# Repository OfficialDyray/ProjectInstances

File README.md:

# Project Instances
A fork of [`HierarchicalPcb`](https://github.com/gauravmm/HierarchicalPcb) which was originally inspired by the [`ReplicateLayout`](https://github.com/MitjaNemec/ReplicateLayout) plugin.

## How To Use

https://github.com/user-attachments/assets/78d0a88c-ed20-4e0c-ae54-b3dcbba4581b

### Create a sub-project:
   1. Creating another (sub-)project inside your main project's folder. 

Here is what the recommended folder structure looks like from the root project:

   3. Create your schematic and pcb in the sub-project like normal
   4. Include the sub-project schematic in your Main Project
   5. Prepare the board like you are about to lay it out.
   6. Run the plugin on the main project's PCB to import the sub-project's PCB

### Update an existing sub-project:
   1. Make your changes to the sub-project's schematic and pcb
   2. Go to your main project and (re)annotate the sub-project's sheet.
   3. Update the pcb from your new schematics
   4. Run the plugin to apply the changes

[A Basic Example](examples/Basic)

## Tips
   1. It is intended to leave footprints out of a sub-board and they won't be laid out in the root project.

## Advanced Usage:
### [Nested Projects](examples/Nesting)
### [Variants of same project](examples/Variants)
### [And more](examples)

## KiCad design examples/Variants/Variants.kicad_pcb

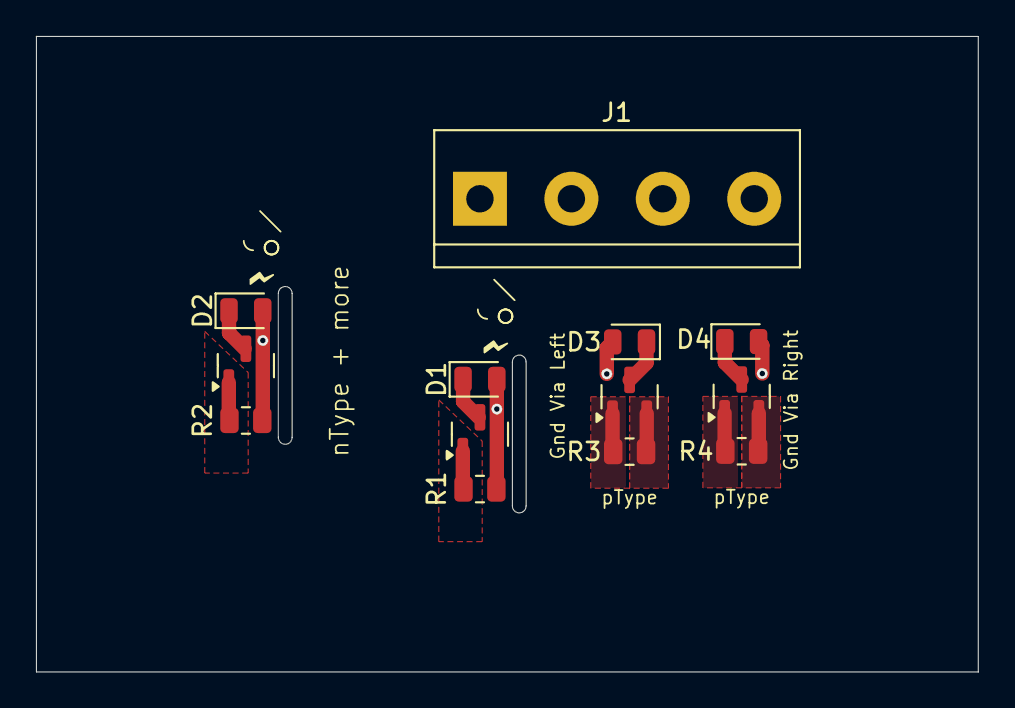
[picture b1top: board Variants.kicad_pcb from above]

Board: 2 copper layers, 52.3 x 35.3 mm, 13 parts (0 on the bottom side), 8 nets.

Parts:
D1, D2, D3, D4: D_Schottky_Small; D_0805_2012Metric
J1: Screw_Terminal_01x04; TerminalBlock_bornier-4_P5.08mm
Q1, Q2: MMBT2222A; SOT-23
Q3, Q4: BC807; SOT-23
R1, R2, R3, R4: 10k; R_0805_2012Metric

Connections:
/Input: Q1.1 (B), R1.1
/nType/Output: D1.1 (K), J1.2, Q1.3 (C), Q3.1 (B), Q4.1 (B), R3.2, R4.2
/nTypeA/Input: Q2.1 (B), R2.1
/nTypeA/Output: D2.1 (K), Q2.3 (C)
/pTypeA/Output: D4.1 (K), J1.3, Q4.3 (C)
/pTypeB/Output: D3.1 (K), J1.1, Q3.3 (C)
GND: D1.2 (A), D2.2 (A), D3.2 (A), D4.2 (A), J1.4, Q1.2 (E), Q2.2 (E), R1.2, R2.2
VDC: Q3.2 (E), Q4.2 (E), R3.1, R4.1

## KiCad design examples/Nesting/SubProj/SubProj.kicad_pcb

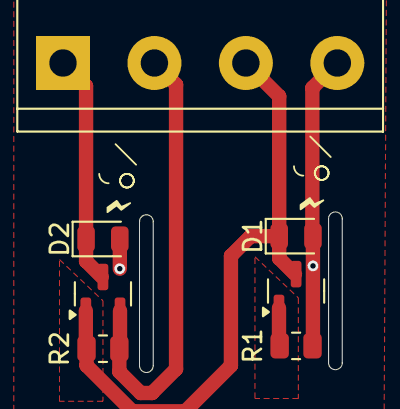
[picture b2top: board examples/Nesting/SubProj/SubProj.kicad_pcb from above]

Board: 2 copper layers, 7 parts (0 on the bottom side), 5 nets.

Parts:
D1, D2: D_Schottky_Small; D_0805_2012Metric
J1: Screw_Terminal_01x04; TerminalBlock_bornier-4_P5.08mm
Q1: MMBT2222A; SOT-23
Q2: BC807; SOT-23
R1, R2: 10k; R_0805_2012Metric

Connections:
/Input: Q1.1 (B), R1.1
/nType/Output: D1.1 (K), J1.3, Q1.3 (C), Q2.1 (B), R2.2
/pType/Output: D2.1 (K), J1.1, Q2.3 (C)
GND: D1.2 (A), D2.2 (A), J1.4, Q1.2 (E), R1.2
VDC: J1.2, Q2.2 (E), R2.1

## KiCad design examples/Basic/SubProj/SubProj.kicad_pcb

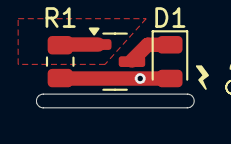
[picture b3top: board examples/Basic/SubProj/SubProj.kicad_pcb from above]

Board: 2 copper layers, 3 parts (0 on the bottom side), 3 nets.

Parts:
D1: D_Schottky_Small; D_0805_2012Metric
Q1: MMBT2222A; SOT-23
R1: 10k; R_0805_2012Metric

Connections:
/Input: Q1.1 (B), R1.1
/Output: D1.1 (K), Q1.3 (C)
GND: D1.2 (A), Q1.2 (E), R1.2

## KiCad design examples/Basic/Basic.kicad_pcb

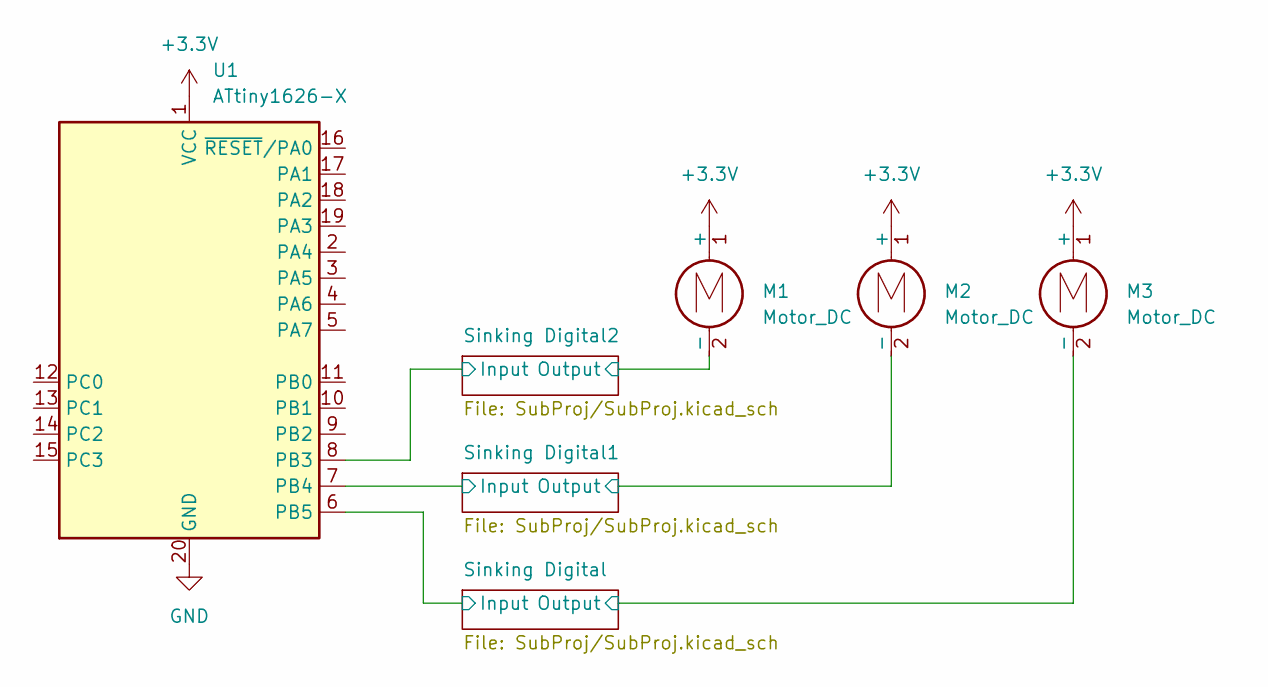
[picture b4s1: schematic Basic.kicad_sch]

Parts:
M1, M2, M3: Motor_DC; PinSocket_1x02_P2.54mm_Vertical
U1: ATtiny1626-X; SSOP-20_5.3x7.2mm_P0.65mm

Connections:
+3.3V: M1.1 (+), M2.1 (+), M3.1 (+), U1.1 (VCC)
/Sinking Digital1/Input: U1.7 (PB4); also elsewhere on the board
/Sinking Digital1/Output: M2.2 (-); also elsewhere on the board
/Sinking Digital2/Input: U1.8 (PB3); also elsewhere on the board
/Sinking Digital2/Output: M1.2 (-); also elsewhere on the board
/Sinking Digital/Input: U1.6 (PB5); also elsewhere on the board
/Sinking Digital/Output: M3.2 (-); also elsewhere on the board
GND: U1.20 (GND); also elsewhere on the board

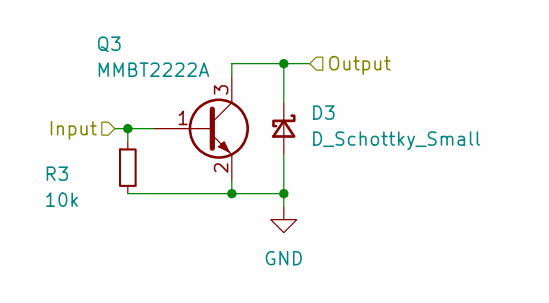
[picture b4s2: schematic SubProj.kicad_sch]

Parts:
D3: D_Schottky_Small; D_0805_2012Metric
Q3: MMBT2222A; SOT-23
R3: 10k; R_0805_2012Metric

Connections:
/Sinking Digital2/Input: Q3.1 (B), R3.1; also elsewhere on the board
/Sinking Digital2/Output: D3.1 (K), Q3.3 (C); also elsewhere on the board
GND: D3.2 (A), Q3.2 (E), R3.2; also elsewhere on the board

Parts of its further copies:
D1, D2: D_Schottky_Small; D_0805_2012Metric
Q1, Q2: MMBT2222A; SOT-23
R1, R2: 10k; R_0805_2012Metric

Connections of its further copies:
/Sinking Digital1/Input: Q2.1 (B), R2.1; also elsewhere on the board
/Sinking Digital1/Output: D2.1 (K), Q2.3 (C); also elsewhere on the board
/Sinking Digital/Input: Q1.1 (B), R1.1; also elsewhere on the board
/Sinking Digital/Output: D1.1 (K), Q1.3 (C); also elsewhere on the board
GND: D1.2 (A), D2.2 (A), Q1.2 (E), Q2.2 (E), R1.2, R2.2; also elsewhere on the board

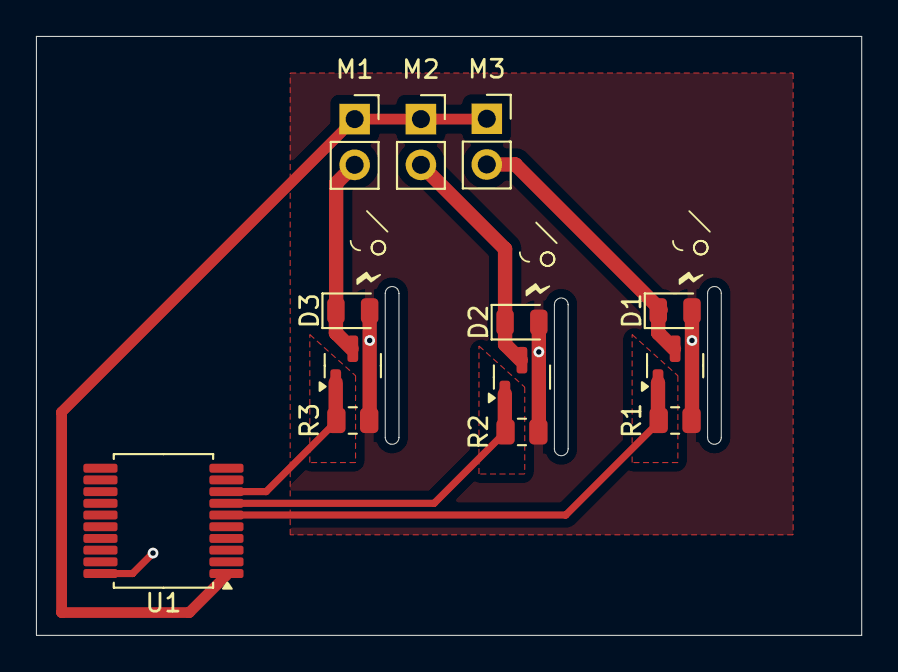
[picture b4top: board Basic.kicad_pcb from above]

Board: 2 copper layers, 45.8 x 33.3 mm, 13 parts (0 on the bottom side), 8 nets.

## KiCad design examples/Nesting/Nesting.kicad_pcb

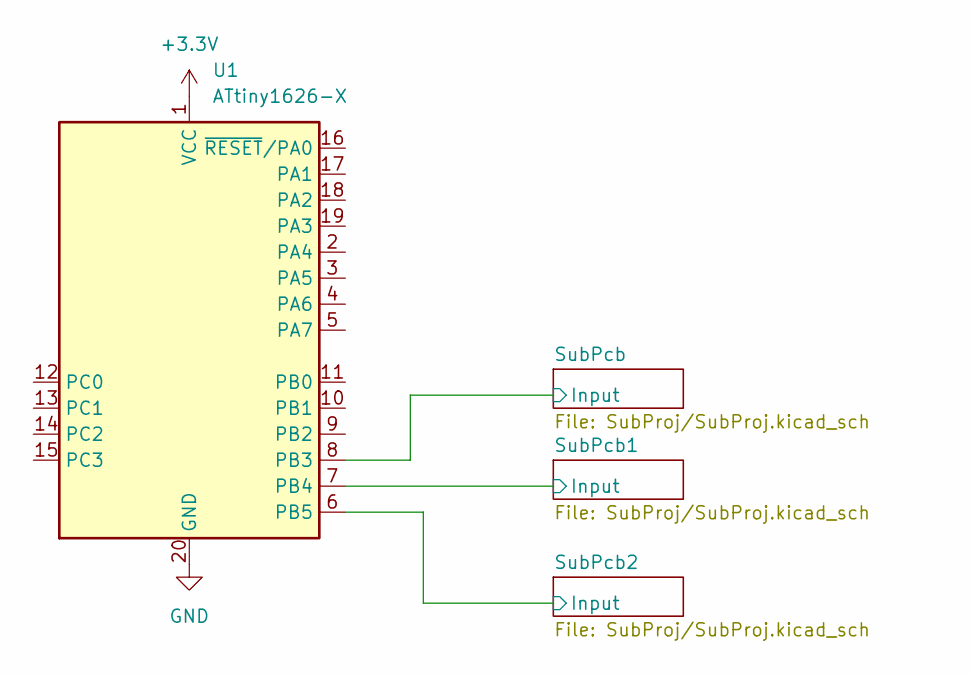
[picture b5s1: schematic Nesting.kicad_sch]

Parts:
U1: ATtiny1626-X; SSOP-20_5.3x7.2mm_P0.65mm

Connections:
+3.3V: U1.1 (VCC)
/SubPcb1/Input: U1.7 (PB4); also elsewhere on the board
/SubPcb2/Input: U1.6 (PB5); also elsewhere on the board
/SubPcb/Input: U1.8 (PB3); also elsewhere on the board
GND: U1.20 (GND); also elsewhere on the board

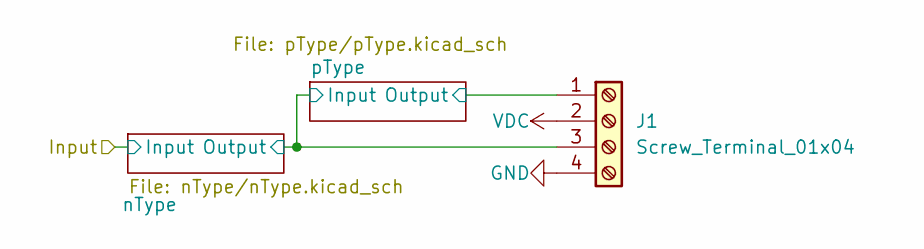
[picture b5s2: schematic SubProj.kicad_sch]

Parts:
J1: Screw_Terminal_01x04; TerminalBlock_bornier-4_P5.08mm

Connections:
/SubPcb/nType/Output: J1.3; also elsewhere on the board
/SubPcb/pType/Output: J1.1; also elsewhere on the board
GND: J1.4; also elsewhere on the board
VDC: J1.2; also elsewhere on the board

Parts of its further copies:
J2, J3: Screw_Terminal_01x04; TerminalBlock_bornier-4_P5.08mm

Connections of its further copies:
/SubPcb1/nType/Output: J2.3; also elsewhere on the board
/SubPcb1/pType/Output: J2.1; also elsewhere on the board
/SubPcb2/nType/Output: J3.3; also elsewhere on the board
/SubPcb2/pType/Output: J3.1; also elsewhere on the board
GND: J2.4, J3.4; also elsewhere on the board
VDC: J2.2, J3.2; also elsewhere on the board

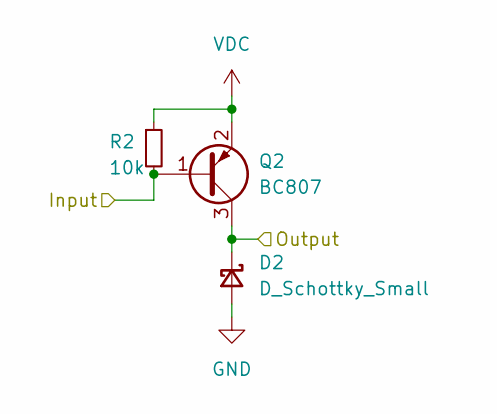
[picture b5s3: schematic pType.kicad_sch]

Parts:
D2: D_Schottky_Small; D_0805_2012Metric
Q2: BC807; SOT-23
R2: 10k; R_0805_2012Metric

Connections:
/SubPcb/nType/Output: Q2.1 (B), R2.2; also elsewhere on the board
/SubPcb/pType/Output: D2.1 (K), Q2.3 (C); also elsewhere on the board
GND: D2.2 (A); also elsewhere on the board
VDC: Q2.2 (E), R2.1; also elsewhere on the board

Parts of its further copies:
D4, D6: D_Schottky_Small; D_0805_2012Metric
Q4, Q6: BC807; SOT-23
R4, R6: 10k; R_0805_2012Metric

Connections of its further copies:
/SubPcb1/nType/Output: Q4.1 (B), R4.2; also elsewhere on the board
/SubPcb1/pType/Output: D4.1 (K), Q4.3 (C); also elsewhere on the board
/SubPcb2/nType/Output: Q6.1 (B), R6.2; also elsewhere on the board
/SubPcb2/pType/Output: D6.1 (K), Q6.3 (C); also elsewhere on the board
GND: D4.2 (A), D6.2 (A); also elsewhere on the board
VDC: Q4.2 (E), Q6.2 (E), R4.1, R6.1; also elsewhere on the board

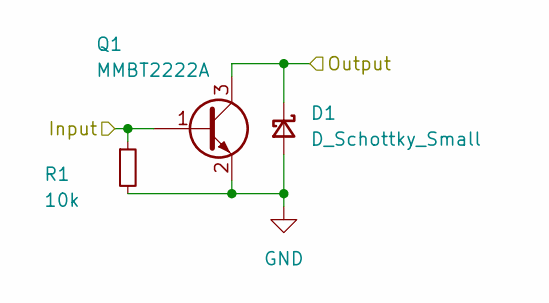
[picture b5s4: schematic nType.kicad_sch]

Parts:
D1: D_Schottky_Small; D_0805_2012Metric
Q1: MMBT2222A; SOT-23
R1: 10k; R_0805_2012Metric

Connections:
/SubPcb/Input: Q1.1 (B), R1.1; also elsewhere on the board
/SubPcb/nType/Output: D1.1 (K), Q1.3 (C); also elsewhere on the board
GND: D1.2 (A), Q1.2 (E), R1.2; also elsewhere on the board

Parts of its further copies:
D3, D5: D_Schottky_Small; D_0805_2012Metric
Q3, Q5: MMBT2222A; SOT-23
R3, R5: 10k; R_0805_2012Metric

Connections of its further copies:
/SubPcb1/Input: Q3.1 (B), R3.1; also elsewhere on the board
/SubPcb1/nType/Output: D3.1 (K), Q3.3 (C); also elsewhere on the board
/SubPcb2/Input: Q5.1 (B), R5.1; also elsewhere on the board
/SubPcb2/nType/Output: D5.1 (K), Q5.3 (C); also elsewhere on the board
GND: D3.2 (A), D5.2 (A), Q3.2 (E), Q5.2 (E), R3.2, R5.2; also elsewhere on the board

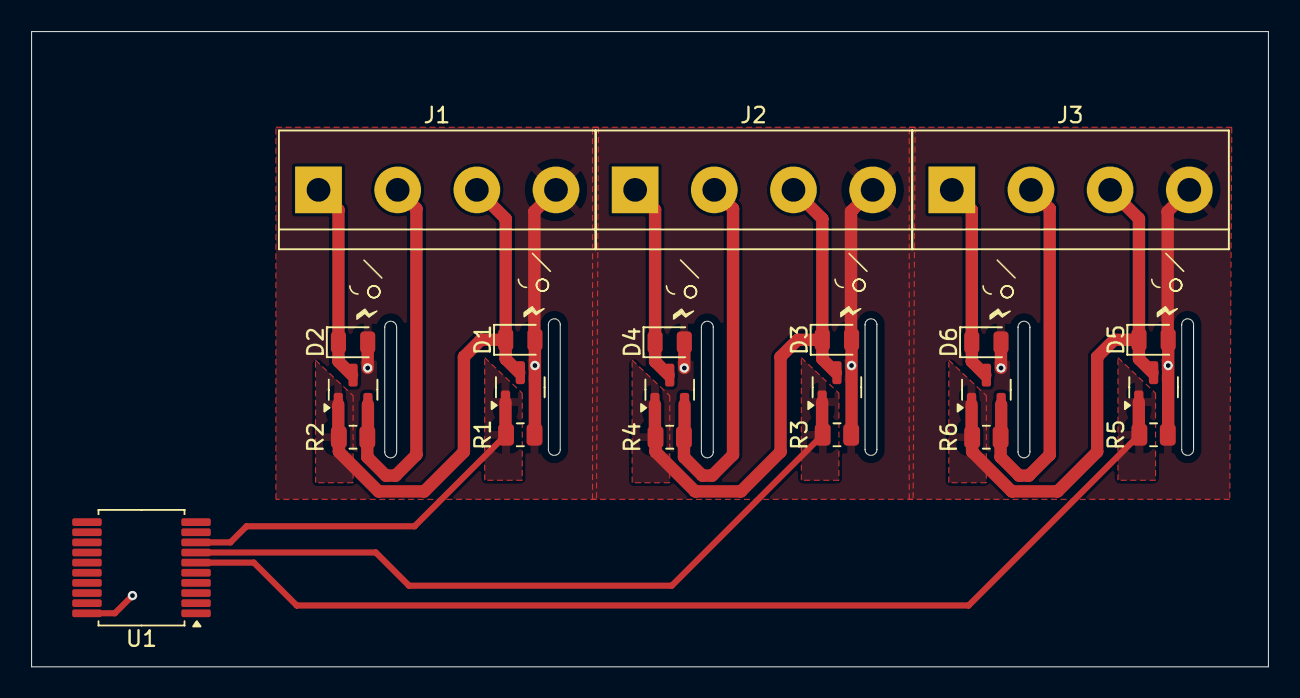
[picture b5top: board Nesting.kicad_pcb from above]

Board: 2 copper layers, 79.4 x 40.8 mm, 22 parts (0 on the bottom side), 11 nets.

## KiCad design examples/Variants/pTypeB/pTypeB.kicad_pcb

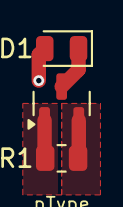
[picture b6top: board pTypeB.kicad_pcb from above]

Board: 2 copper layers, 3 parts (0 on the bottom side), 3 nets.

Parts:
D1: D_Schottky_Small; D_0805_2012Metric
Q1: BC807; SOT-23
R1: 10k; R_0805_2012Metric

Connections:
/Input: Q1.1 (B), R1.2
/Output: D1.1 (K), Q1.3 (C)
VDC: Q1.2 (E), R1.1

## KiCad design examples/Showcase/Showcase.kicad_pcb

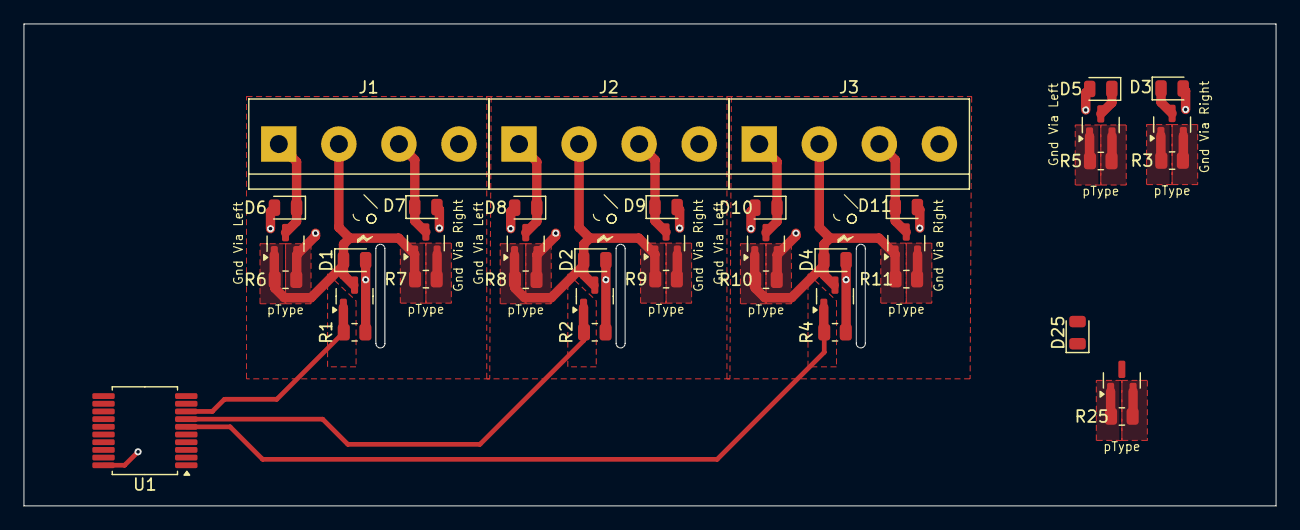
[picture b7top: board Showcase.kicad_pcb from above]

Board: 2 copper layers, 105.9 x 40.8 mm, 40 parts (0 on the bottom side), 20 nets.

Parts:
D1, D2, D3, D4, D5, D6, D7, D8, D9, D10, D11, D25: D_Schottky_Small; D_0805_2012Metric
J1, J2, J3: Screw_Terminal_01x04; TerminalBlock_bornier-4_P5.08mm
Q1, Q2, Q4: MMBT2222A; SOT-23
Q3, Q5, Q6, Q7, Q8, Q9, Q10, Q11, Q25: BC807; SOT-23
R1, R2, R3, R4, R5, R6, R7, R8, R9, R10, R11, R25: 10k; R_0805_2012Metric
U1: ATtiny1626-X; SSOP-20_5.3x7.2mm_P0.65mm

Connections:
/SubPcb1/Input: Q2.1 (B), R2.1, U1.7 (PB4)
/SubPcb1/nType/Output: D2.1 (K), J2.2, Q2.3 (C), Q8.1 (B), Q9.1 (B), R8.2, R9.2
/SubPcb1/pTypeA/Output: D9.1 (K), J2.3, Q9.3 (C)
/SubPcb1/pTypeB/Output: D8.1 (K), J2.1, Q8.3 (C)
/SubPcb2/Input: Q4.1 (B), R4.1, U1.6 (PB5)
/SubPcb2/nType/Output: D4.1 (K), J3.2, Q4.3 (C), Q10.1 (B), Q11.1 (B), R10.2, R11.2
/SubPcb2/pTypeA/Output: D11.1 (K), J3.3, Q11.3 (C)
/SubPcb2/pTypeB/Output: D10.1 (K), J3.1, Q10.3 (C)
/SubPcb/Input: Q1.1 (B), R1.1, U1.8 (PB3)
/SubPcb/nType/Output: D1.1 (K), J1.2, Q1.3 (C), Q6.1 (B), Q7.1 (B), R6.2, R7.2
/SubPcb/pTypeA/Output: D7.1 (K), J1.3, Q7.3 (C)
/SubPcb/pTypeB/Output: D6.1 (K), J1.1, Q6.3 (C)
/pType/Input: Q25.1 (B), R25.2
/pType/Output: D25.1 (K), Q25.3 (C)
/pTypeA1/Input: Q3.1 (B), R3.2
/pTypeA1/Output: D3.1 (K), Q3.3 (C)
/pTypeB1/Input: Q5.1 (B), R5.2
/pTypeB1/Output: D5.1 (K), Q5.3 (C)
GND: D1.2 (A), D2.2 (A), D3.2 (A), D4.2 (A), D5.2 (A), D6.2 (A), D7.2 (A), D8.2 (A), D9.2 (A), D10.2 (A), D11.2 (A), D25.2 (A), J1.4, J2.4, J3.4, Q1.2 (E), Q2.2 (E), Q4.2 (E), R1.2, R2.2, R4.2, U1.20 (GND)
VDC: Q3.2 (E), Q5.2 (E), Q6.2 (E), Q7.2 (E), Q8.2 (E), Q9.2 (E), Q10.2 (E), Q11.2 (E), Q25.2 (E), R3.1, R5.1, R6.1, R7.1, R8.1, R9.1, R10.1, R11.1, R25.1

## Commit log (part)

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2024-03-22 🐛 fix first item not showing in TreeList
2024-03-22 🐛 fix AppendNet not needed in KiCad 8
2024-03-22 fix: footprint text rotation if not similar to footprint rotation
2024-03-22 feat: use ✅ and ❌ instead of font weight change
2024-03-22 feat: sort items and improve labels
2024-03-22 feat: hide unusable sheets
2024-03-22 fix: remove fix that did not fix things
2024-05-16 Remove Recursion
2024-05-17 Add Zones to Examples
2024-05-17 Better Net Assign
2024-05-19 Expermental parser
2024-05-19 Interface Revamp
2024-05-19 Restructure (again)
2024-05-20 betterCleanSingleLists
2024-05-20 Use custom parser instead
2024-05-21 remove parser class
2024-05-21 Rewrite begin
2024-05-26 combine placement and hdata
2024-05-28 Shotgun changes
2024-05-29 More shotgunning
2024-05-29 Squash
2024-05-29 Working State
2024-05-29 Switch Parser
2024-05-29 Gui Tri state
2024-05-30 More Examples Bug Fixes
2024-05-31 Rename + Cleanup
2024-05-31 Out of bounds
2024-05-31 Project Cleanup
2024-05-31 Invalid Board Crash
2024-05-31 Accidental commit
2024-06-01 Ui column rename
2024-12-22 New Impliment. Todo:Gui
2024-12-24 bug hunting
2024-12-24 example clean + screenshots
2024-12-25 Update README.md with video
2025-05-13 Field Delete Crash Fix
2025-05-13 LocalZoneConnection
2025-07-21 Update hdata.py to prevent group naming collision
    Having nested schematics like this caused problems
    ```
    + Root
    +-+ A
    | +-+ B
    | +-+ B1
2025-09-13 Remove Match-Case
2026-01-28 Fix FileNotFoundError message to use sheetPath
2026-02-01 fix(parser): handle non-ASCII schematics to avoid ASCII decode crash
    KiCad schematics containing non-ASCII characters were failing to load on
    macOS with `UnicodeDecodeError: 'ascii' codec can't decode byte 0xc2` in
    `sexpdata.load()`. Open schematics as UTF-8 and fall back to Latin-1.
2026-02-01 chore(gitignore): document macOS .DS_Store ignore
2026-03-03 fix(hdata): add warning for failed board file loading in SheetFile class
2026-03-29 Arc Track FIx
